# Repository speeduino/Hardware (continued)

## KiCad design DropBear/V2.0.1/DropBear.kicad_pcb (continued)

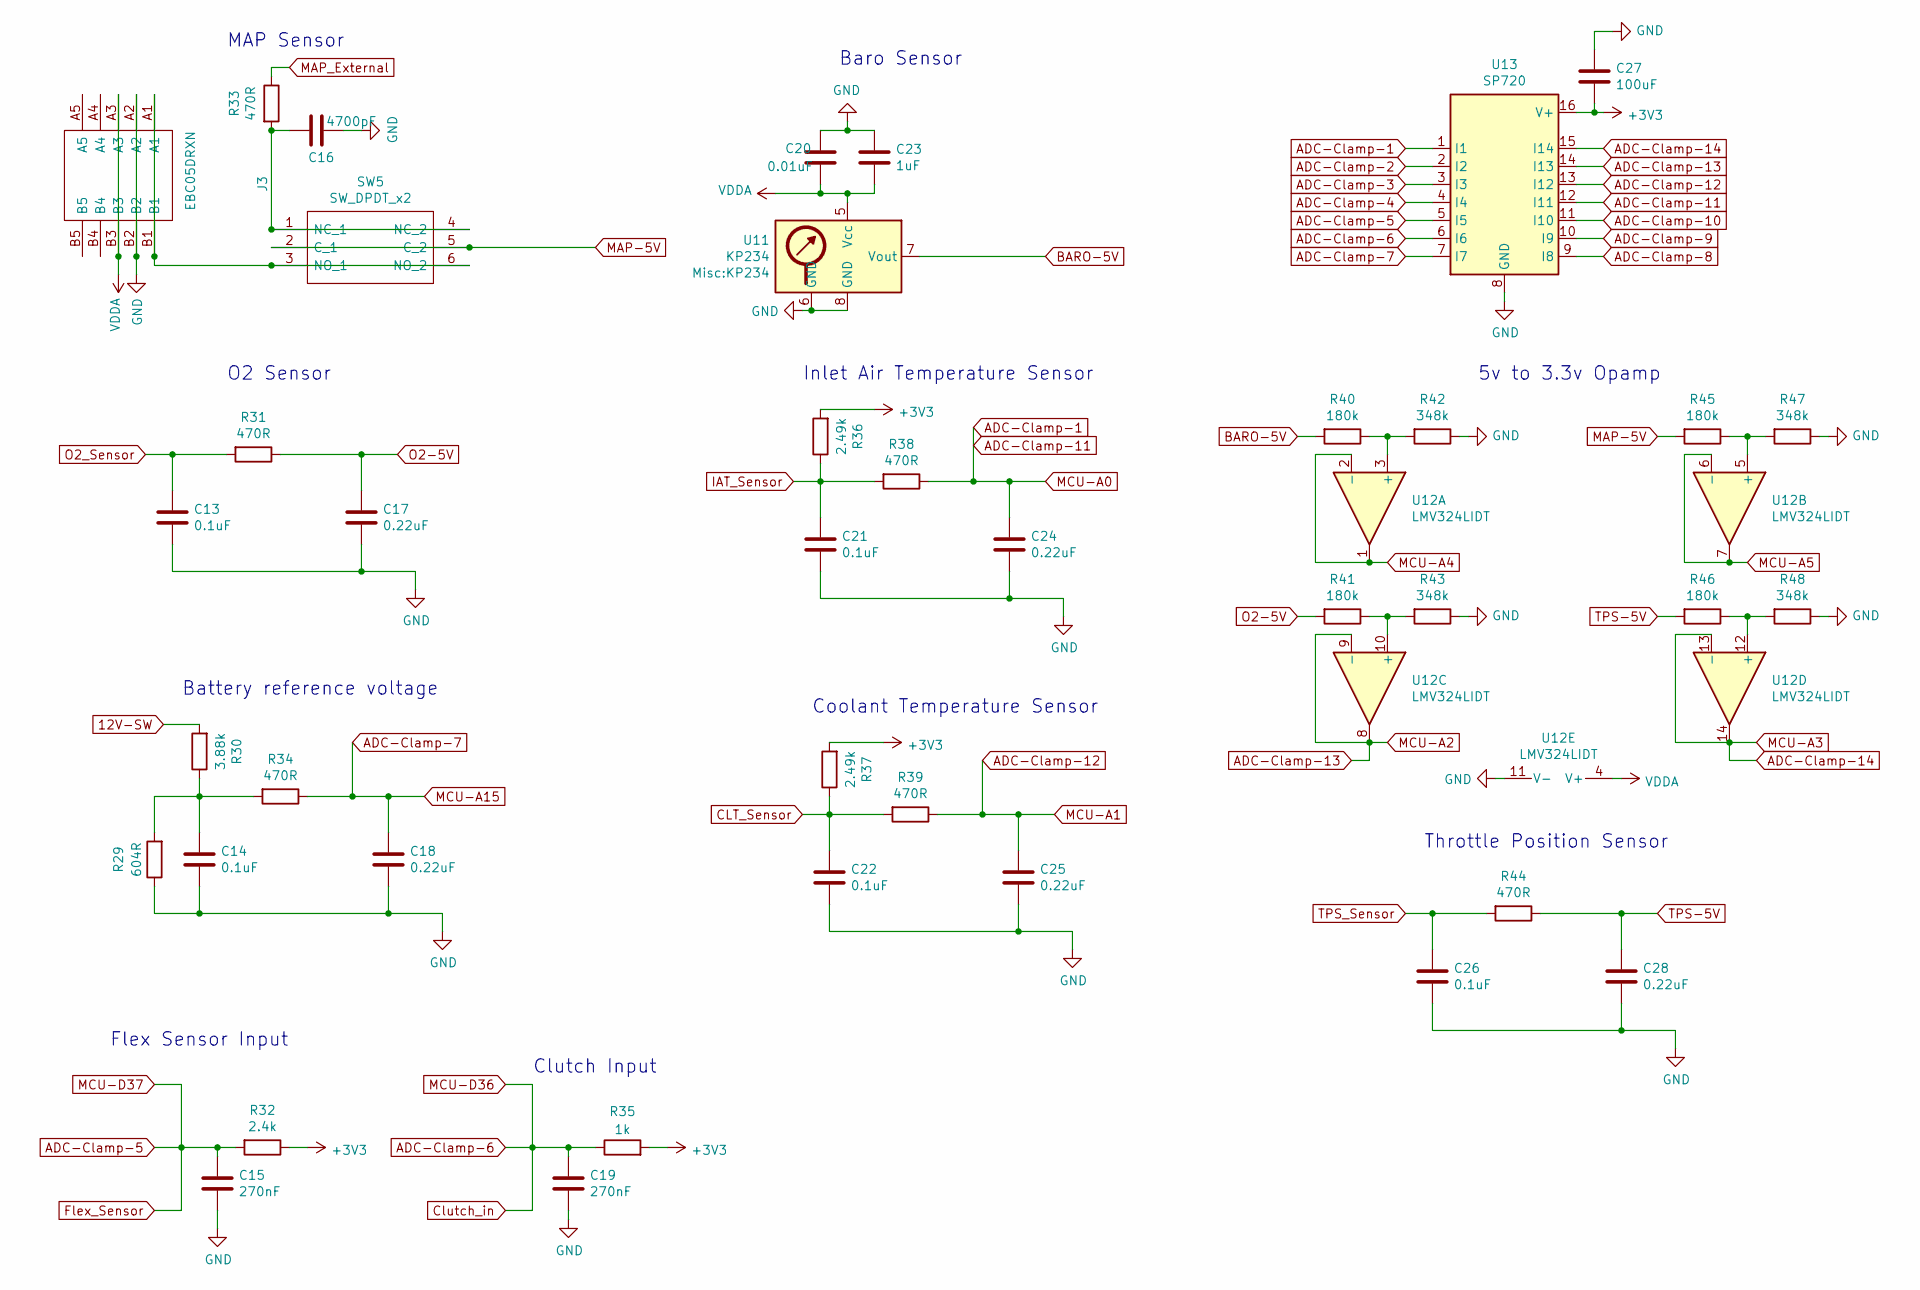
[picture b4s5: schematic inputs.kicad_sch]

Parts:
C13, C14, C21, C22, C26: 0.1uF; C_0805_2012Metric; Manufacturer_Part_Number CC0805KRX7R9BB104; Digikey Part Number 311-1140-1-ND
C15, C19: 270nF; C_0805_2012Metric; Manufacturer_Part_Number CC0805JRX7R7BB274; Digikey Part Number 311-4268-1-ND
C16: 4700pF; C_0805_2012Metric; Manufacturer_Part_Number CC0805KRX7R9BB472; Digikey Part Number 311-1133-1-ND
C17, C18, C24, C25, C28: 0.22uF; C_0805_2012Metric; Manufacturer_Part_Number CL21B224KOCNNNC; Digikey Part Number 1276-1284-1-ND
C20: 0.01uF; C_0805_2012Metric; Manufacturer_Part_Number CC0805KRX7R9BB103; Digikey Part Number 311-1136-1-ND
C23: 1uF; C_0805_2012Metric; Manufacturer_Part_Number CC0805KKX7R7BB105; Digikey Part Number 311-1365-1-ND
C27: 100uF; C_1206_3216Metric; Manufacturer_Part_Number CL31A107MQHNNNE; Digikey Part Number 1276-1782-1-ND
J3: EBC05DRXN; Manufacturer_Part_Number EBC05DRXN; Digikey Part Number S9641-ND
R29: 604R; R_0805_2012Metric; Tolerance 1%; Manufacturer_Part_Number RC0805FR-07604RL; Digikey Part Number 311-604CRCT-ND
R30: 3.88k; R_0603_1608Metric_Pad0.98x0.95mm_HandSolder; Tolerance 1%; Manufacturer_Part_Number RT0603BRD073K88L; Digikey Part Number YAG4550CT-ND
R31, R33, R34, R38, R39, R44: 470R; R_0805_2012Metric; Manufacturer_Part_Number ERJ-6ENF4700V; Digikey Part Number P470CCT-ND
R32: 2.4k; R_0805_2012Metric; Manufacturer_Part_Number RC0805FR-072K4L; Digikey Part Number 311-2.40KCRCT-ND
R35: 1k; R_0805_2012Metric; Manufacturer_Part_Number RC0805FR-071KL; Digikey Part Number 311-1.00KCRCT-ND
R36, R37: 2.49k; R_0805_2012Metric; Tolerance 0.1%; Manufacturer_Part_Number RT0805BRD072K49L; Digikey Part Number YAG1854CT-ND
R40, R41, R45, R46: 180k; R_0805_2012Metric; Manufacturer_Part_Number RC0805FR-07180KL; Digikey Part Number 311-180KCRCT-ND
R42, R43, R47, R48: 348k; R_0805_2012Metric; Manufacturer_Part_Number ERJ-6ENF3483V; Digikey Part Number P348KCDKR-ND
SW5: SW_DPDT_x2; AYZ0202AGRLC; Manufacturer_Part_Number AYZ0202AGRLC; Digikey Part Number 401-2013-1-ND
U11: KP234; Manufacturer_Part_Number KP234XTMA1; Digikey Part Number 448-KP234XTMA1CT-ND
U12: LMV324LIDT; SOIC-14_3.9x8.7mm_P1.27mm; Manufacturer_Part_Number LMV324LIDT; Digikey Part Number 497-13052-1-ND
U13: SP720; SOIC-16_3.9x9.9mm_P1.27mm; Manufacturer_Part_Number SP720ABTG; Digikey Part Number F3162CT-ND

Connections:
12V-SW: R30.2; also elsewhere on the board
+3V3: C27.2, R32.1, R35.2, R36.2, R37.2, U13.16 (V+); also elsewhere on the board
ADC-Clamp-1: C24.1, R38.1, U13.1 (I1), U13.12 (I11); also elsewhere on the board
ADC-Clamp-3: U13.3 (I3)
ADC-Clamp-4: U13.4 (I4); also elsewhere on the board
ADC-Clamp-5: C15.1, R32.2, U13.5 (I5); also elsewhere on the board
ADC-Clamp-6: C19.1, R35.1, U13.6 (I6); also elsewhere on the board
ADC-Clamp-7: C18.1, R34.1, U13.7 (I7); also elsewhere on the board
ADC-Clamp-8: U13.9 (I8)
ADC-Clamp-9: U13.10 (I9)
ADC-Clamp-10: U13.2 (I2), U13.11 (I10); also elsewhere on the board
ADC-Clamp-12: C25.1, R39.1, U13.13 (I12); also elsewhere on the board
ADC-Clamp-13: U12.8, U12.9 (-), U13.14 (I13); also elsewhere on the board
ADC-Clamp-14: U12.13 (-), U12.14, U13.15 (I14); also elsewhere on the board
BARO-5V: R40.2, U11.7 (Vout)
CLT_Sensor: C22.1, R37.1, R39.2; also elsewhere on the board
GND: C13.2, C14.2, C15.2, C16.1, C17.2, C18.2, C19.2, C20.1, C21.2, C22.2, C23.1, C24.2, C25.2, C26.2, C27.1, C28.2, J3.A2, J3.B2, R29.1, R42.1, R43.1, R47.1, R48.1, U11.6 (GND), U11.8 (GND), U12.11 (V-), U13.8 (GND); also elsewhere on the board
IAT_Sensor: C21.1, R36.1, R38.2; also elsewhere on the board
MAP-5V: R45.2, SW5.2 (C_1), SW5.5 (C_2)
MAP_External: R33.1; also elsewhere on the board
MCU-A4: U12.1, U12.2 (-); also elsewhere on the board
MCU-A5: U12.6 (-), U12.7; also elsewhere on the board
unnamed: C14.1, R29.2, R30.1, R34.2
unnamed: C16.2, R33.2, SW5.1 (NC_1), SW5.4 (NC_2)
unnamed: J3.A1, J3.B1, SW5.3 (NO_1), SW5.6 (NO_2)
unnamed: R40.1, R42.2, U12.3 (+)
unnamed: R45.1, R47.2, U12.5 (+)
unnamed: R41.1, R43.2, U12.10 (+)
unnamed: R46.1, R48.2, U12.12 (+)
O2-5V: C17.1, R31.1, R41.2
O2_Sensor: C13.1, R31.2; also elsewhere on the board
TPS-5V: C28.1, R44.1, R46.2
TPS_Sensor: C26.1, R44.2; also elsewhere on the board
VDDA: C20.2, C23.2, J3.A3, J3.B3, U11.5 (Vcc), U12.4 (V+); also elsewhere on the board

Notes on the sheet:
5v to 3.3v Opamp
Inlet Air Temperature Sensor
Battery reference voltage
Flex Sensor Input
Coolant Temperature Sensor
Throttle Position Sensor
Baro Sensor
Clutch Input
MAP Sensor
O2 Sensor

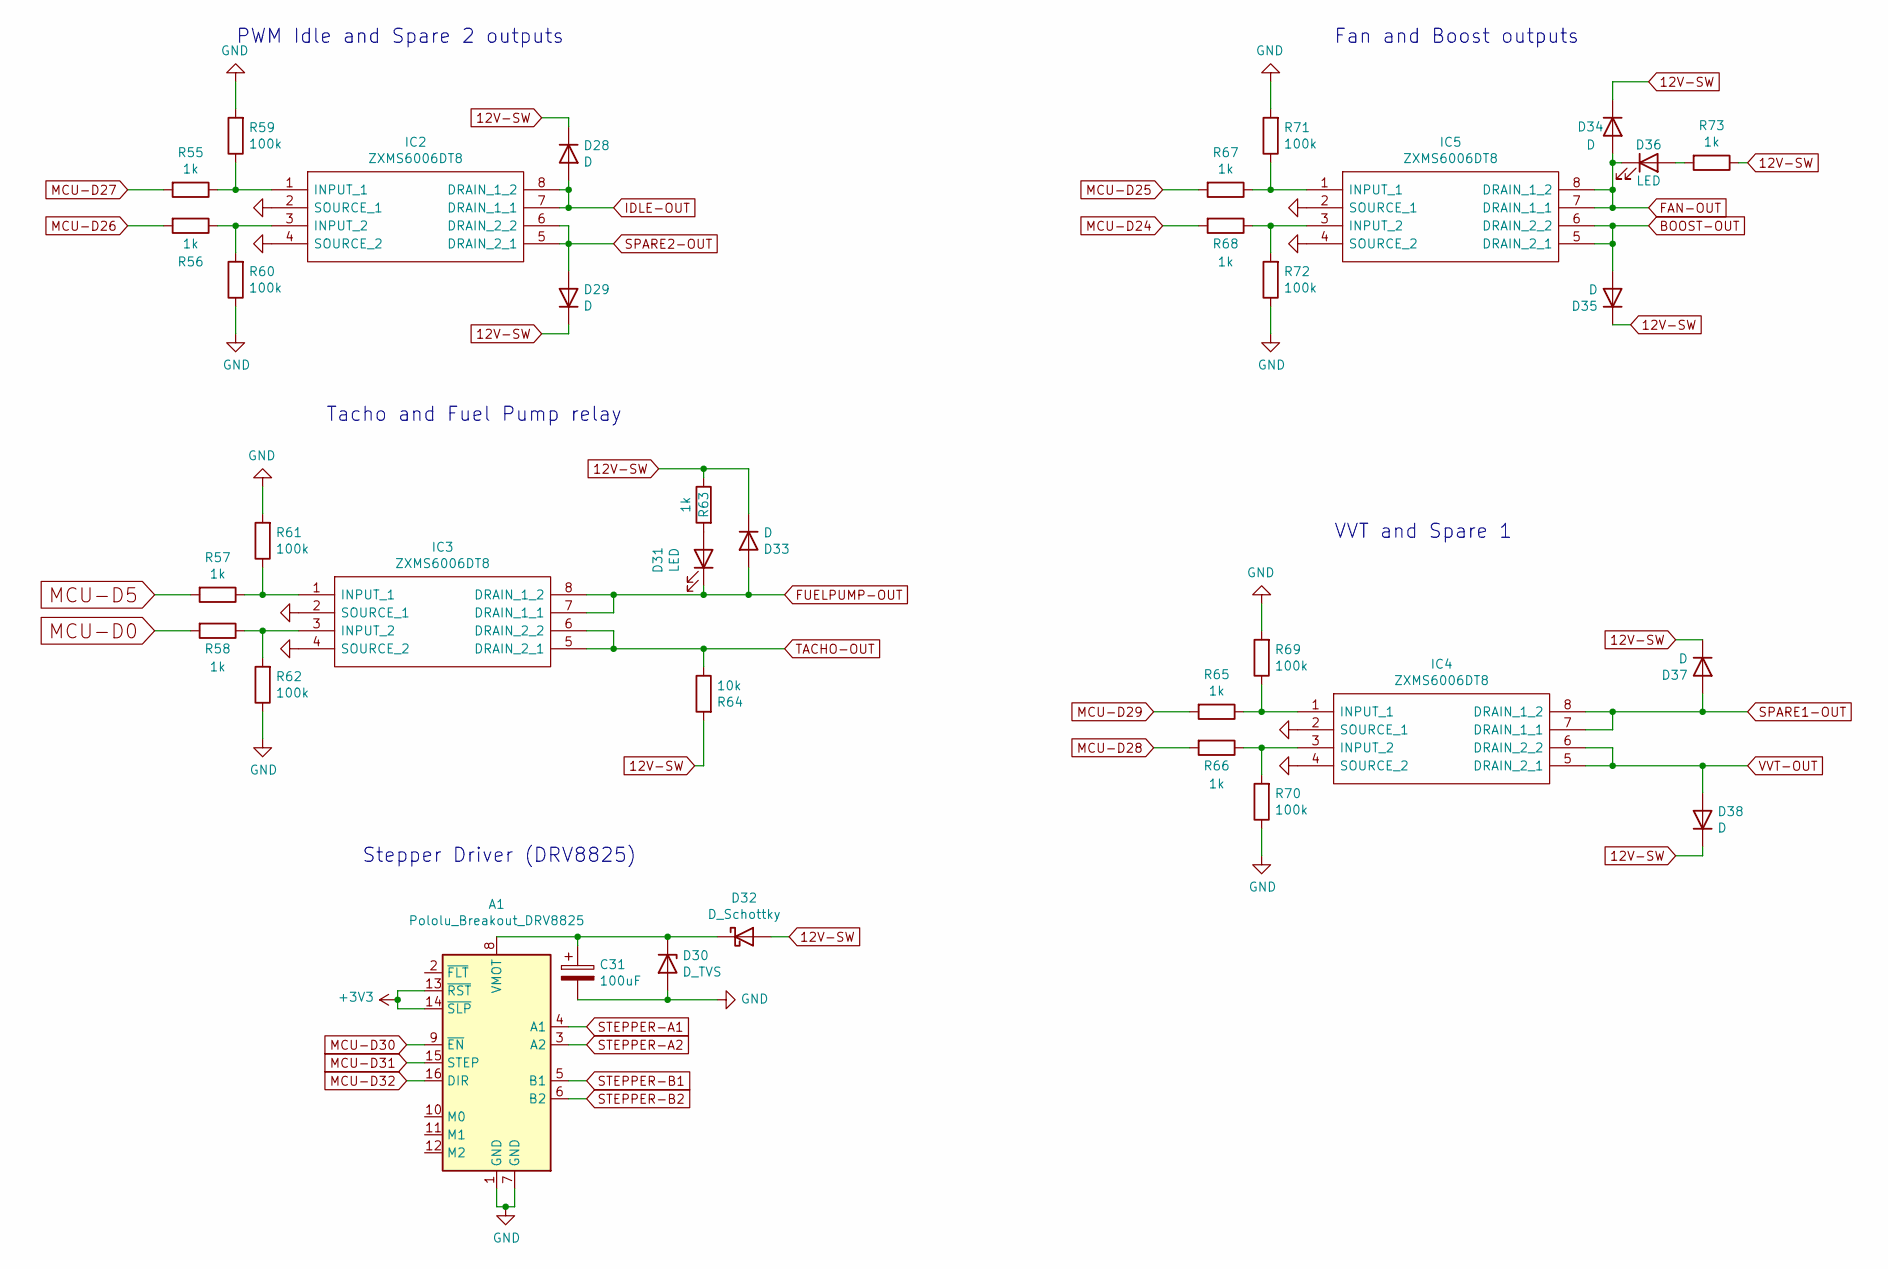
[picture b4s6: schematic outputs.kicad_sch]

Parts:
A1: Pololu_Breakout_DRV8825; Pololu_Breakout-16_15.2x20.3mm
C31: 100uF; CP_Elec_6.3x7.7; Manufacturer_Part_Number EEE-FT1V101AV; Digikey Part Number P124821CT-ND
D28, D29, D33, D34, D35, D37, D38: D; D_SOD-323; Manufacturer_Part_Number 1N4448WX-TP; Digikey Part Number 1N4448WXTPMSCT-ND
D30: D_TVS; D_SOD-123F; Manufacturer_Part_Number PTVS20VS1UR,115; Digikey Part Number 1727-5865-1-ND
D31: LED; LED_0805_2012Metric; Manufacturer_Part_Number LG R971-KN-1; Digikey Part Number 475-1410-2-ND
D32: D_Schottky; D_PowerDI-123; Manufacturer_Part_Number DFLS2100-7; Digikey Part Number DFLS2100-7DICT-ND
D36: LED; LED_0805_2012Metric; Manufacturer_Part_Number LH R974-LP-1; Digikey Part Number 475-1415-1-ND
IC2, IC3, IC4, IC5: ZXMS6006DT8; Diodes_SM8; Manufacturer_Part_Number ZXMS6006DT8; Digikey Part Number ZXMS6006DT8TADICT-ND
R55, R56, R57, R58, R63, R65, R66, R67, R68, R73: 1k; R_0805_2012Metric; Manufacturer_Part_Number RC0805FR-071KL; Digikey Part Number 311-1.00KCRCT-ND
R59, R60, R61, R62, R69, R70, R71, R72: 100k; R_0805_2012Metric; Manufacturer_Part_Number RC0805FR-07100KL; Digikey Part Number 311-100KCRCT-ND
R64: 10k; R_0805_2012Metric; Manufacturer_Part_Number RC0805JR-0710KL; Digikey Part Number 311-10KARCT-ND

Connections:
12V-SW: D28.1 (K), D29.1 (K), D32.2 (A), D33.1 (K), D34.1 (K), D35.1 (K), D37.1 (K), D38.1 (K), R63.1, R64.2, R73.1; also elsewhere on the board
+3V3: A1.13 (~RST), A1.14 (~SLP); also elsewhere on the board
BOOST-OUT: D35.2 (A), IC5.5 (DRAIN_2_1), IC5.6 (DRAIN_2_2); also elsewhere on the board
FAN-OUT: D34.2 (A), D36.1 (K), IC5.7 (DRAIN_1_1), IC5.8 (DRAIN_1_2); also elsewhere on the board
FUELPUMP-OUT: D31.1 (K), D33.2 (A), IC3.7 (DRAIN_1_1), IC3.8 (DRAIN_1_2); also elsewhere on the board
GND: A1.1 (GND), A1.7 (GND), C31.2, D30.2 (A), IC2.2 (SOURCE_1), IC2.4 (SOURCE_2), IC3.2 (SOURCE_1), IC3.4 (SOURCE_2), IC4.2 (SOURCE_1), IC4.4 (SOURCE_2), IC5.2 (SOURCE_1), IC5.4 (SOURCE_2), R59.2, R60.1, R61.2, R62.1, R69.2, R70.1, R71.2, R72.1; also elsewhere on the board
IDLE-OUT: A1.5 (B1), D28.2 (A), IC2.7 (DRAIN_1_1), IC2.8 (DRAIN_1_2); also elsewhere on the board
MCU-D0: R58.2; also elsewhere on the board
MCU-D5: R57.2; also elsewhere on the board
MCU-D24: R68.2; also elsewhere on the board
MCU-D25: R67.2; also elsewhere on the board
MCU-D26: R56.2; also elsewhere on the board
MCU-D27: R55.2; also elsewhere on the board
MCU-D28: R66.2; also elsewhere on the board
MCU-D29: R65.2; also elsewhere on the board
MCU-D30: A1.9 (~EN); also elsewhere on the board
MCU-D31: A1.15 (STEP); also elsewhere on the board
MCU-D32: A1.16 (DIR); also elsewhere on the board
unnamed: A1.8 (VMOT), C31.1, D30.1 (K), D32.1 (K)
unnamed: D31.2 (A), R63.2
unnamed: D36.2 (A), R73.2
unnamed: IC2.1 (INPUT_1), R55.1, R59.1
unnamed: IC2.3 (INPUT_2), R56.1, R60.2
unnamed: IC3.1 (INPUT_1), R57.1, R61.1
unnamed: IC3.3 (INPUT_2), R58.1, R62.2
unnamed: IC4.1 (INPUT_1), R65.1, R69.1
unnamed: IC4.3 (INPUT_2), R66.1, R70.2
unnamed: IC5.1 (INPUT_1), R67.1, R71.1
unnamed: IC5.3 (INPUT_2), R68.1, R72.2
SPARE1-OUT: A1.3 (A2), D37.2 (A), IC4.7 (DRAIN_1_1), IC4.8 (DRAIN_1_2); also elsewhere on the board
SPARE2-OUT: A1.6 (B2), D29.2 (A), IC2.5 (DRAIN_2_1), IC2.6 (DRAIN_2_2); also elsewhere on the board
STEPPER-A1: A1.4 (A1), D38.2 (A), IC4.5 (DRAIN_2_1), IC4.6 (DRAIN_2_2); also elsewhere on the board
TACHO-OUT: IC3.5 (DRAIN_2_1), IC3.6 (DRAIN_2_2), R64.1; also elsewhere on the board

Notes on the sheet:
Tacho and Fuel Pump relay
Fan and Boost outputs
PWM Idle and Spare 2 outputs
VVT and Spare 1
Stepper Driver (DRV8825)

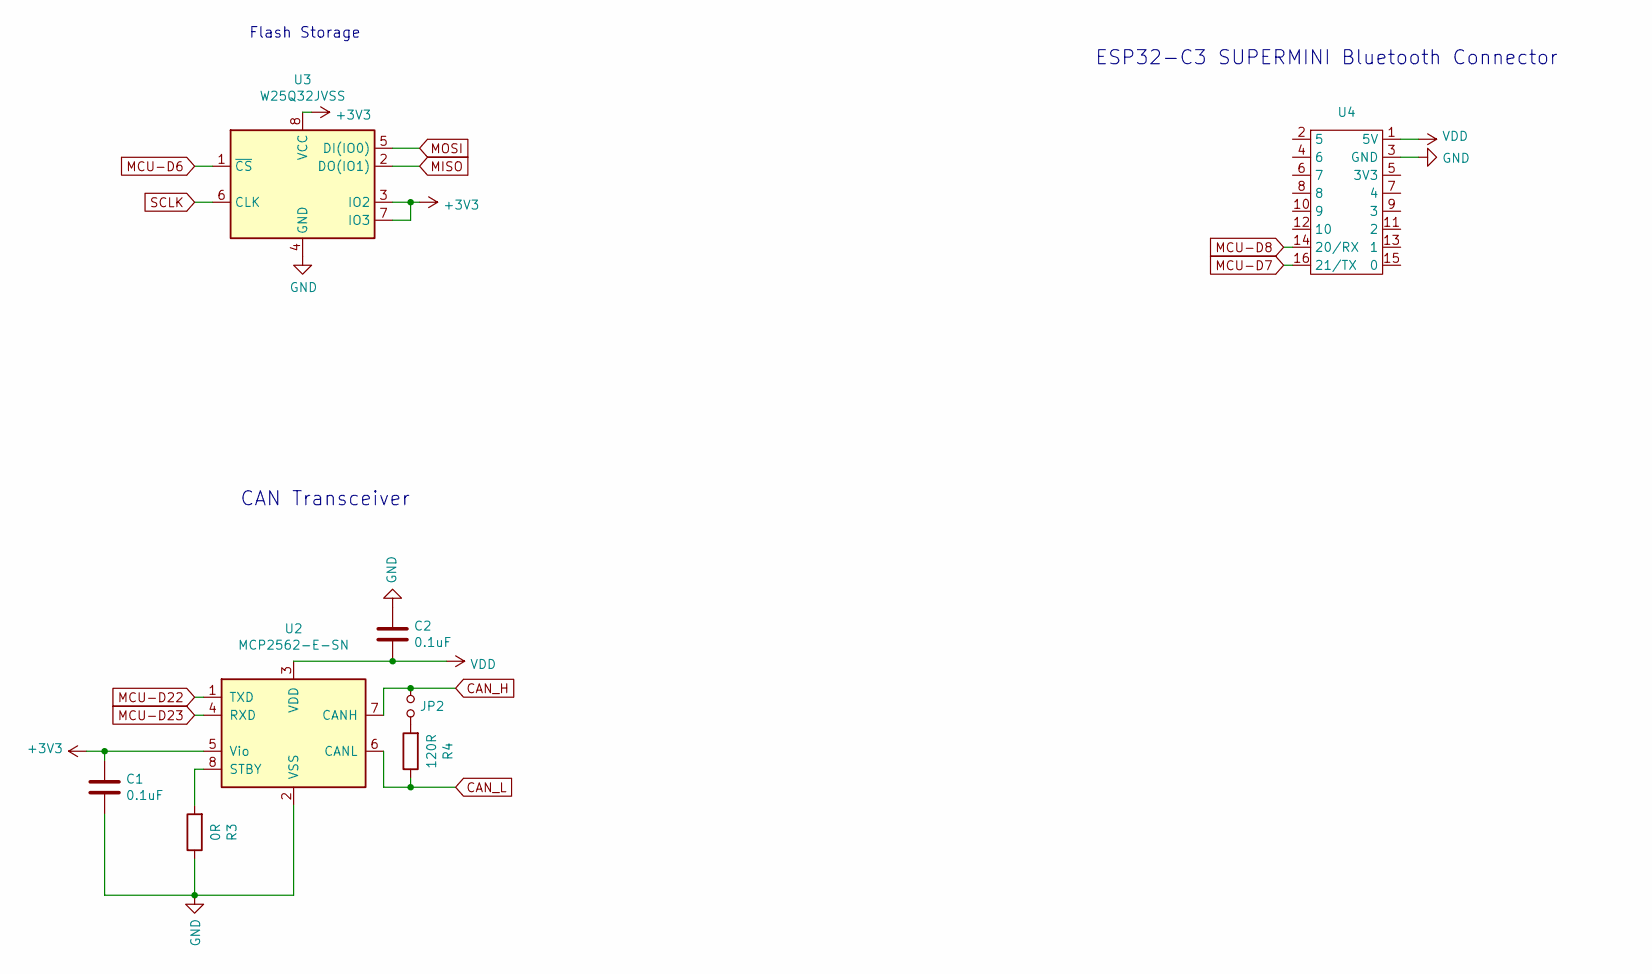
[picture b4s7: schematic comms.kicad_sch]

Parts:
C1, C2: 0.1uF; C_0805_2012Metric; Manufacturer_Part_Number CC0805KRX7R9BB104; Digikey Part Number 311-1140-1-ND
JP2: Jumper_NO_Small; SolderJumper-2_P1.3mm_Open_Pad1.0x1.5mm
R3: 0R; R_0805_2012Metric; Manufacturer_Part_Number RC0805JR-070RL; Digikey Part Number 311-0.0ARCT-ND
R4: 120R; R_0805_2012Metric; Manufacturer_Part_Number RC0805FR-07120RL; Digikey Part Number 311-120CRCT-ND
U2: MCP2562-E-SN; SOIC-8_3.9x4.9mm_P1.27mm; Manufacturer_Part_Number MCP2562-E/SN; Digikey Part Number MCP2562-E/SN-ND
U3: W25Q32JVSS; SOIC-8_5.23x5.23mm_P1.27mm; Manufacturer_Part_Number W25Q32JVSSIQ; Digikey Part Number W25Q32JVSSIQCT-ND
U4: ESP32-C3 SUPERMINI

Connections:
+3V3: C1.1, U2.5 (Vio), U3.3 (IO2), U3.7 (IO3), U3.8 (VCC); also elsewhere on the board
+5V: C2.2, U2.3 (VDD), U4.1 (5V); also elsewhere on the board
CAN_H: JP2.1, U2.7 (CANH); also elsewhere on the board
CAN_L: R4.1, U2.6 (CANL); also elsewhere on the board
GND: C1.2, C2.1, R3.1, U2.2 (VSS), U3.4 (GND), U4.3 (GND); also elsewhere on the board
MCU-A8: U2.1 (TXD); also elsewhere on the board
MCU-A9: U2.4 (RXD); also elsewhere on the board
MCU-D6: U3.1 (~CS); also elsewhere on the board
MCU-D7: U4.16 (21/TX); also elsewhere on the board
MCU-D8: U4.14 (20/RX); also elsewhere on the board
MISO: U3.2 (DO(IO1)); also elsewhere on the board
MOSI: U3.5 (DI(IO0)); also elsewhere on the board
unnamed: JP2.2, R4.2
unnamed: R3.2, U2.8 (STBY)
SCLK: U3.6 (CLK); also elsewhere on the board

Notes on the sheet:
Flash Storage
CAN Transceiver
ESP32-C3 SUPERMINI Bluetooth Connector

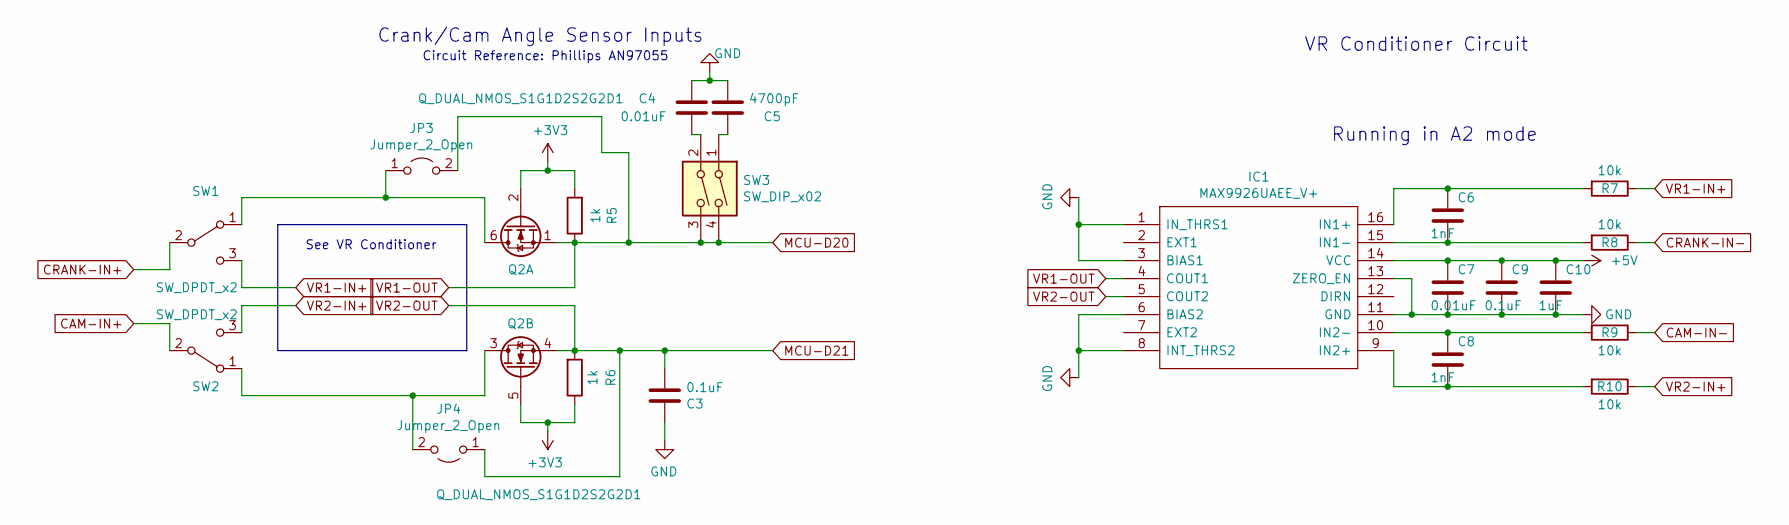
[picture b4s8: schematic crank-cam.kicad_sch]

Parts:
C3, C9: 0.1uF; C_0805_2012Metric; Manufacturer_Part_Number CC0805KRX7R9BB104; Digikey Part Number 311-1140-1-ND
C4, C7: 0.01uF; C_0805_2012Metric; Manufacturer_Part_Number CC0805KRX7R9BB103; Digikey Part Number 311-1136-1-ND
C5: 4700pF; C_0805_2012Metric; Manufacturer_Part_Number CC0805KRX7R9BB472; Digikey Part Number 311-1133-1-ND
C6, C8: 1nF; C_0805_2012Metric; Manufacturer_Part_Number C0805C102J5HACAUTO; Digikey Part Number 399-16591-1-ND
C10: 1uF; C_0805_2012Metric; Manufacturer_Part_Number CC0805KKX7R7BB105; Digikey Part Number 311-1365-1-ND
IC1: MAX9926UAEE_V+; QSOP-16_3.9x4.9mm_P0.635mm; Manufacturer_Part_Number MAX9926UAEE/V+; Mouser Part Number 700-MAX9926UAEE/V+
JP3, JP4: Jumper_2_Open; SolderJumper-2_P1.3mm_Open_Pad1.0x1.5mm
Q2: Q_DUAL_NMOS_S1G1D2S2G2D1; SOT-363_SC-70-6; Manufacturer_Part_Number NVJD5121NT1G; Digikey Part Number NVJD5121NT1GOSCT-ND
R5, R6: 1k; R_0805_2012Metric; Manufacturer_Part_Number RC0805FR-071KL; Digikey Part Number 311-1.00KCRCT-ND
R7, R8, R9, R10: 10k; R_1206_3216Metric; Manufacturer_Part_Number RC1206FR-7W10KL; Digikey Part Number 13-RC1206FR-7W10KLTR-ND
SW1, SW2: SW_DPDT_x2; AYZ0202AGRLC; Manufacturer_Part_Number AYZ0202AGRLC; Digikey Part Number 401-2013-1-ND
SW3: SW_DIP_x02; SW_DIP_SPSTx02_Slide_9.78x7.26mm_W8.61mm_P2.54mm; Manufacturer_Part_Number IKN0204000; Digikey Part Number 679-3566-1-ND

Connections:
+3V3: Q2.2 (G), Q2.5 (G), R5.2, R6.1; also elsewhere on the board
+5V: C7.1, C9.1, C10.1, IC1.14 (VCC); also elsewhere on the board
CAM-IN+: SW2.2 (B); also elsewhere on the board
CAM-IN-: R9.1; also elsewhere on the board
CRANK-IN+: SW1.2 (B); also elsewhere on the board
CRANK-IN-: R8.1; also elsewhere on the board
GND: C3.1, C4.1, C5.2, C7.2, C9.2, C10.2, IC1.1 (IN_THRS1), IC1.3 (BIAS1), IC1.6 (BIAS2), IC1.8 (INT_THRS2), IC1.11 (GND), IC1.13 (ZERO_EN); also elsewhere on the board
MCU-A6: IC1.4 (COUT1), JP3.2 (B), Q2.1 (S), R5.1, SW3.3, SW3.4; also elsewhere on the board
MCU-A7: C3.2, IC1.5 (COUT2), JP4.1 (A), Q2.4 (S), R6.2; also elsewhere on the board
unnamed: C4.2, SW3.2
unnamed: C5.1, SW3.1
unnamed: C6.1, IC1.16 (IN1+), R7.2
unnamed: C6.2, IC1.15 (IN1-), R8.2
unnamed: C8.2, IC1.9 (IN2+), R10.2
unnamed: C8.1, IC1.10 (IN2-), R9.2
unnamed: JP3.1 (A), Q2.6 (D), SW1.1 (A)
unnamed: JP4.2 (B), Q2.3 (D), SW2.1 (A)
VR1-IN+: R7.1, SW1.3 (C)
VR2-IN+: R10.1, SW2.3 (C)

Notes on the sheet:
Running in A2 mode
VR Conditioner Circuit
Crank/Cam Angle Sensor Inputs
See VR Conditioner
Circuit Reference: Phillips AN97055

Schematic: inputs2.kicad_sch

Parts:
C29, C30: 0.01uF; C_0805_2012Metric; Manufacturer_Part_Number CC0805KRX7R9BB103; Digikey Part Number 311-1136-1-ND
D26, D27: D_TVS; D_SOD-523; Manufacturer_Part_Number D1213A-01T-7; Digikey Part Number D1213A-01T-7DITR-ND
Q3: Q_DUAL_NMOS_S1G1D2S2G2D1; SOT-363_SC-70-6; Manufacturer_Part_Number NVJD5121NT1G; Digikey Part Number NVJD5121NT1GOSCT-ND
R49, R52: 1k; R_0805_2012Metric; Manufacturer_Part_Number RC0805FR-071KL; Digikey Part Number 311-1.00KCRCT-ND
R50, R53: 180k; R_0805_2012Metric; Manufacturer_Part_Number RC0805FR-07180KL; Digikey Part Number 311-180KCRCT-ND
R51, R54: 348k; R_0805_2012Metric; Manufacturer_Part_Number ERJ-6ENF3483V; Digikey Part Number P348KCDKR-ND
U14: LMV324LIDT; SOIC-14_3.9x8.7mm_P1.27mm; Manufacturer_Part_Number LMV324LIDT; Digikey Part Number 497-13052-1-ND

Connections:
+3V3: Q3.2 (G), Q3.5 (G), R49.2, R52.2; also elsewhere on the board
ADC-Clamp-4: U14.1, U14.2 (-); also elsewhere on the board
ADC-Clamp-10: U14.6 (-), U14.7; also elsewhere on the board
GND: C29.1, C30.1, D26.2 (A2), D27.2 (A2), R51.1, R54.1, U14.11 (V-); also elsewhere on the board
MCU-D34: C30.2, D27.1 (A1), Q3.4 (S), R52.1; also elsewhere on the board
MCU-D35: C29.2, D26.1 (A1), Q3.1 (S), R49.1; also elsewhere on the board
unnamed: R50.1, R51.2, U14.3 (+)
unnamed: R53.1, R54.2, U14.5 (+)
unnamed: U14.8, U14.9 (-)
unnamed: U14.13 (-), U14.14
SPARE1-Digital: Q3.6 (D); also elsewhere on the board
SPARE1_Sensor: R50.2; also elsewhere on the board
SPARE2-Digital: Q3.3 (D); also elsewhere on the board
SPARE2_Sensor: R53.2; also elsewhere on the board
VDDA: U14.4 (V+); also elsewhere on the board

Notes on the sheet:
5v to 3.3v Opamp
Second O2 sensor should be on Spare 2 if in use
Spare digital inputs

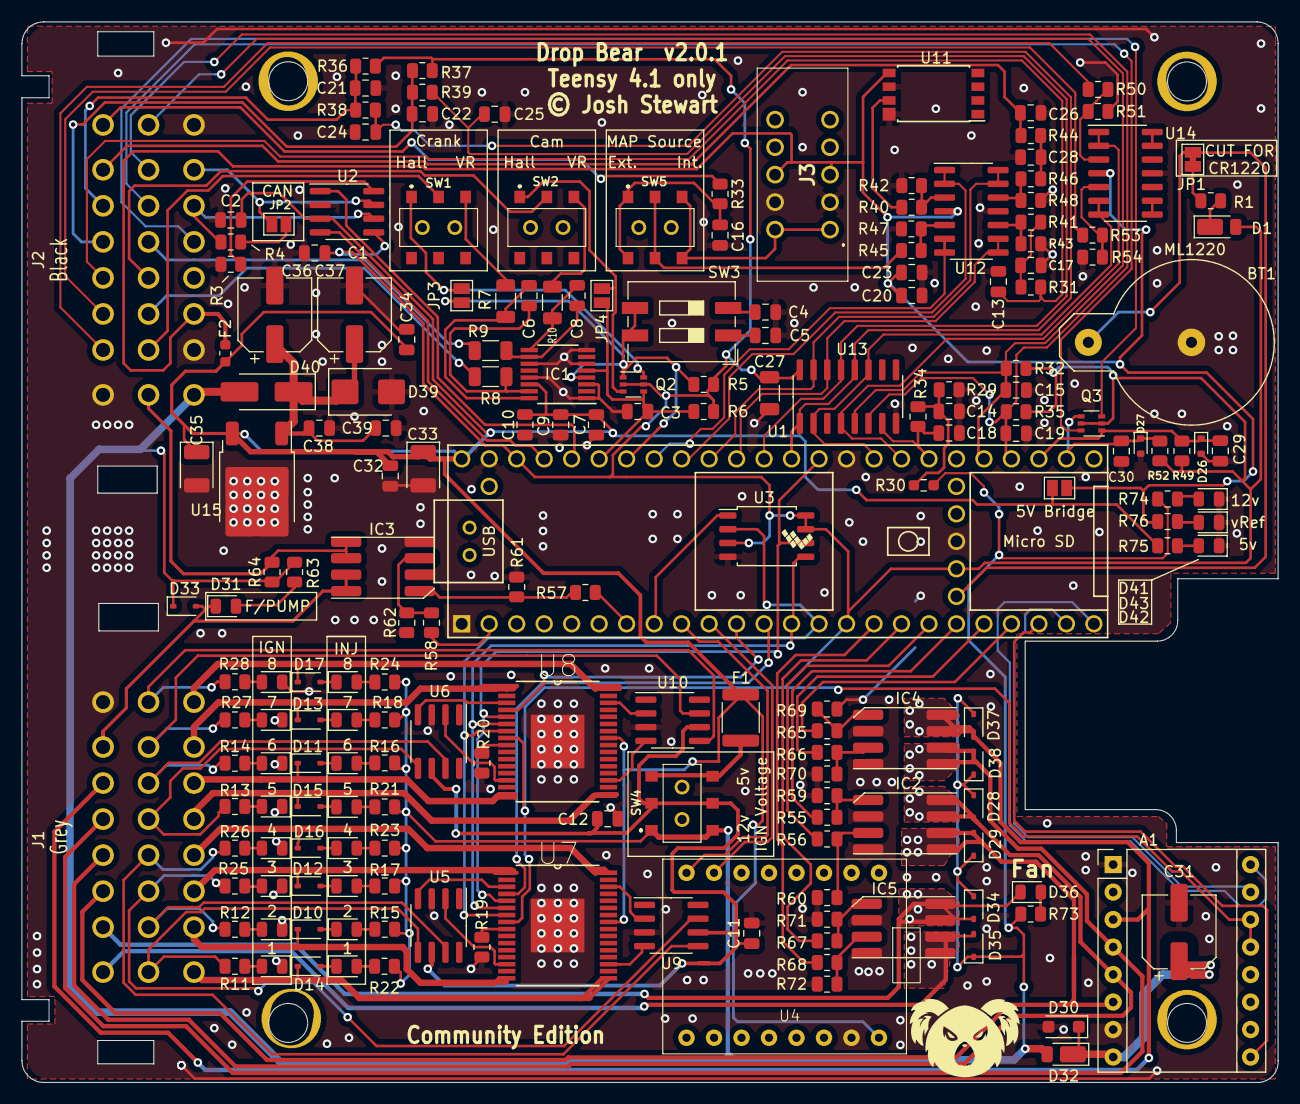
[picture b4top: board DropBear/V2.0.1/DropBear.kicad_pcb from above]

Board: 2 copper layers, 116.1 x 98.0 mm, 196 parts (0 on the bottom side), 161 nets.

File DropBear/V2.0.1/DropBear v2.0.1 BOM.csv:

Comment,Designator,Footprint,LCSC
"Pololu_Breakout_DRV8825","A1","Module:Pololu_Breakout-16_15.2x20.3mm",""
"Battery_Cell","BT1","Battery:BatteryHolder_Keystone_500",""
"0.1uF","C1,C2,C3,C9,C12,C13,C14,C21,C22,C26,C32,C34,C38","Capacitor_SMD:C_0805_2012Metric",""
"1uF","C10,C11,C23","Capacitor_SMD:C_0805_2012Metric",""
"270nF","C15,C19","Capacitor_SMD:C_0805_2012Metric",""
"0.22uF","C17,C18,C24,C25,C28","Capacitor_SMD:C_0805_2012Metric",""
"100uF","C27","Capacitor_SMD:C_1206_3216Metric",""
"100uF","C31","Capacitor_SMD:CP_Elec_6.3x7.7",""
"47uF","C33,C35","Capacitor_Tantalum_SMD:CP_EIA-3528-21_Kemet-B",""
"33uF","C36,C37","Capacitor_SMD:CP_Elec_6.3x7.7",""
"0.33uF","C39","Capacitor_SMD:C_0805_2012Metric",""
"0.01uF","C4,C7,C20,C29,C30","Capacitor_SMD:C_0805_2012Metric",""
"4700pF","C5,C16","Capacitor_SMD:C_0805_2012Metric",""
"1nF","C6,C8","Capacitor_SMD:C_0805_2012Metric",""
"D_Schottky","D1,D32","Diode_SMD:D_PowerDI-123",""
"D","D10,D11,D12,D13,D14,D15,D16,D17,D28,D29,D33,D34,D35,D37,D38","Diode_SMD:D_SOD-323",""
"LED","D2,D3,D4,D5,D6,D7,D8,D9,D18,D19,D20,D21,D22,D23,D24,D25,D31,D36,D41,D42,D43","LED_SMD:LED_0805_2012Metric",""
"D_TVS","D26,D27","Diode_SMD:D_SOD-523",""
"D_TVS","D30","Diode_SMD:D_SOD-123F",""
"D_TVS","D39","Diode_SMD:D_SMB",""
"D_Schottky","D40","Diode_SMD:D_SMA_Handsoldering",""
"Polyfuse","F1","Fuse:Fuse_1812_4532Metric",""
"Polyfuse","F2","Fuse:Fuse_0603_1608Metric",""
"MAX9926UAEE_V+","IC1","Package_SO:QSOP-16_3.9x4.9mm_P0.635mm",""
"ZXMS6006DT8","IC2,IC3,IC4,IC5","IC_Automotive:Diodes_SM8",""
"Delphi_Sicma_24","J1","Connector_Automotive:Delphi_Sicma_24_Grey",""
"Delphi_Sicma_24","J2","Connector_Automotive:Delphi_Sicma_24_Black",""
"EBC05DRXN","J3","Misc:EBC05DRXN",""
"SolderJumper_2_Bridged","JP1","Jumper:SolderJumper-2_P1.3mm_Bridged_Pad1.0x1.5mm",""
"Jumper_NO_Small","JP2","Jumper:SolderJumper-2_P1.3mm_Open_Pad1.0x1.5mm",""
"Jumper_2_Open","JP3,JP4,JP5","Jumper:SolderJumper-2_P1.3mm_Open_Pad1.0x1.5mm",""
"Q_DUAL_NMOS_S1G1D2S2G2D1","Q2,Q3","Package_TO_SOT_SMD:SOT-363_SC-70-6",""
"470R","R1,R31,R33,R34,R38,R39,R44","Resistor_SMD:R_0805_2012Metric",""
"10k","R19,R20,R64","Resistor_SMD:R_0805_2012Metric",""
"604R","R29","Resistor_SMD:R_0805_2012Metric",""
"0R","R3","Resistor_SMD:R_0805_2012Metric",""
"3.88k","R30","Resistor_SMD:R_0603_1608Metric_Pad0.98x0.95mm_HandSolder",""
"2.4k","R32","Resistor_SMD:R_0805_2012Metric",""
"2.49k","R36,R37,R74","Resistor_SMD:R_0805_2012Metric",""
"120R","R4","Resistor_SMD:R_0805_2012Metric",""
"180k","R40,R41,R45,R46,R50,R53","Resistor_SMD:R_0805_2012Metric",""
"348k","R42,R43,R47,R48,R51,R54","Resistor_SMD:R_0805_2012Metric",""
"1k","R5,R6,R11,R12,R13,R14,R15,R16,R17,R18,R21,R22,R23,R24,R25,R26,R27,R28,R35,R49,R52,R55,R56,R57,R58,R63,R65,R66,R67,R68,R73,R75,R76","Resistor_SMD:R_0805_2012Metric",""
"100k","R59,R60,R61,R62,R69,R70,R71,R72","Resistor_SMD:R_0805_2012Metric",""
"10k","R7,R8,R9,R10","Resistor_SMD:R_1206_3216Metric",""
"SW_DPDT_x2","SW1,SW2,SW4,SW5","Misc:AYZ0202AGRLC",""
"SW_DIP_x02","SW3","Button_Switch_SMD:SW_DIP_SPSTx02_Slide_9.78x7.26mm_W8.61mm_P2.54mm",""
"Teensy4.1","U1","Shields:Teensy41",""
"KP234","U11","Misc:KP234",""
"LMV324LIDT","U12,U14","Package_SO:SOIC-14_3.9x8.7mm_P1.27mm",""
"SP720","U13","Package_SO:SOIC-16_3.9x9.9mm_P1.27mm",""
"MC78M05_TO252","U15","Package_TO_SOT_SMD:TO-252-2",""
"MCP2562-E-SN","U2","Package_SO:SOIC-8_3.9x4.9mm_P1.27mm",""
"W25Q32JVSS","U3","Package_SO:SOIC-8_5.23x5.23mm_P1.27mm",""
"~","U4","Misc:ESP32-C3 SUPERMINI",""
"TC4424A","U5,U6,U9,U10","Package_SO:SOIC-8_3.9x4.9mm_P1.27mm",""
"MC33810","U7,U8","IC_Automotive:SOIC32-P0.65-33N",""
